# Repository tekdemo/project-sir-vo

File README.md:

SirVo Project
=============

A servo motor replacement board that runs a magnetic encoder for continuous rotation without loss of tracking. Runs the Arduino environment on an embedded Atmega 328, exposing hardware PWM capture, I2C, and UART to a 4 wire input cable.

Additionally, allows for a header on the back of the motor controller, with the intention that you could include "backpacks" that extend the functionality much like you do with an Arduino Shield. 

Uses OpenServo board footprint, which should fit some medium size servo controllers. Tested on Parallax Continuus Rotation Servo, and looks like it should fit TowerPro MG995 servos (which require modifications for continuous rotation).

Currently in the testing phase, with several known flaws in the hardware

Known Bugs
============

- H bridge needs a proper driver for operation with higher input voltages. 

- Voltage regulator isn't performing satisfactorially, and needs to be replaced. Currently requires external 3.3V supply to function.

- Code still very unfinished (and hence, not posted). The exception is the [AS5050 Library](https://github.com/tekdemo/AS5050), which is reasonably functional.

- Motor slot alignments are still not known to function on all brands of servos, but work well for now.

- This uses a very strange passive multiplexing scheme I hacked together for the I2C and UART lines. It's been confirmed to work for UART data transmissions, but I2C is still untested.

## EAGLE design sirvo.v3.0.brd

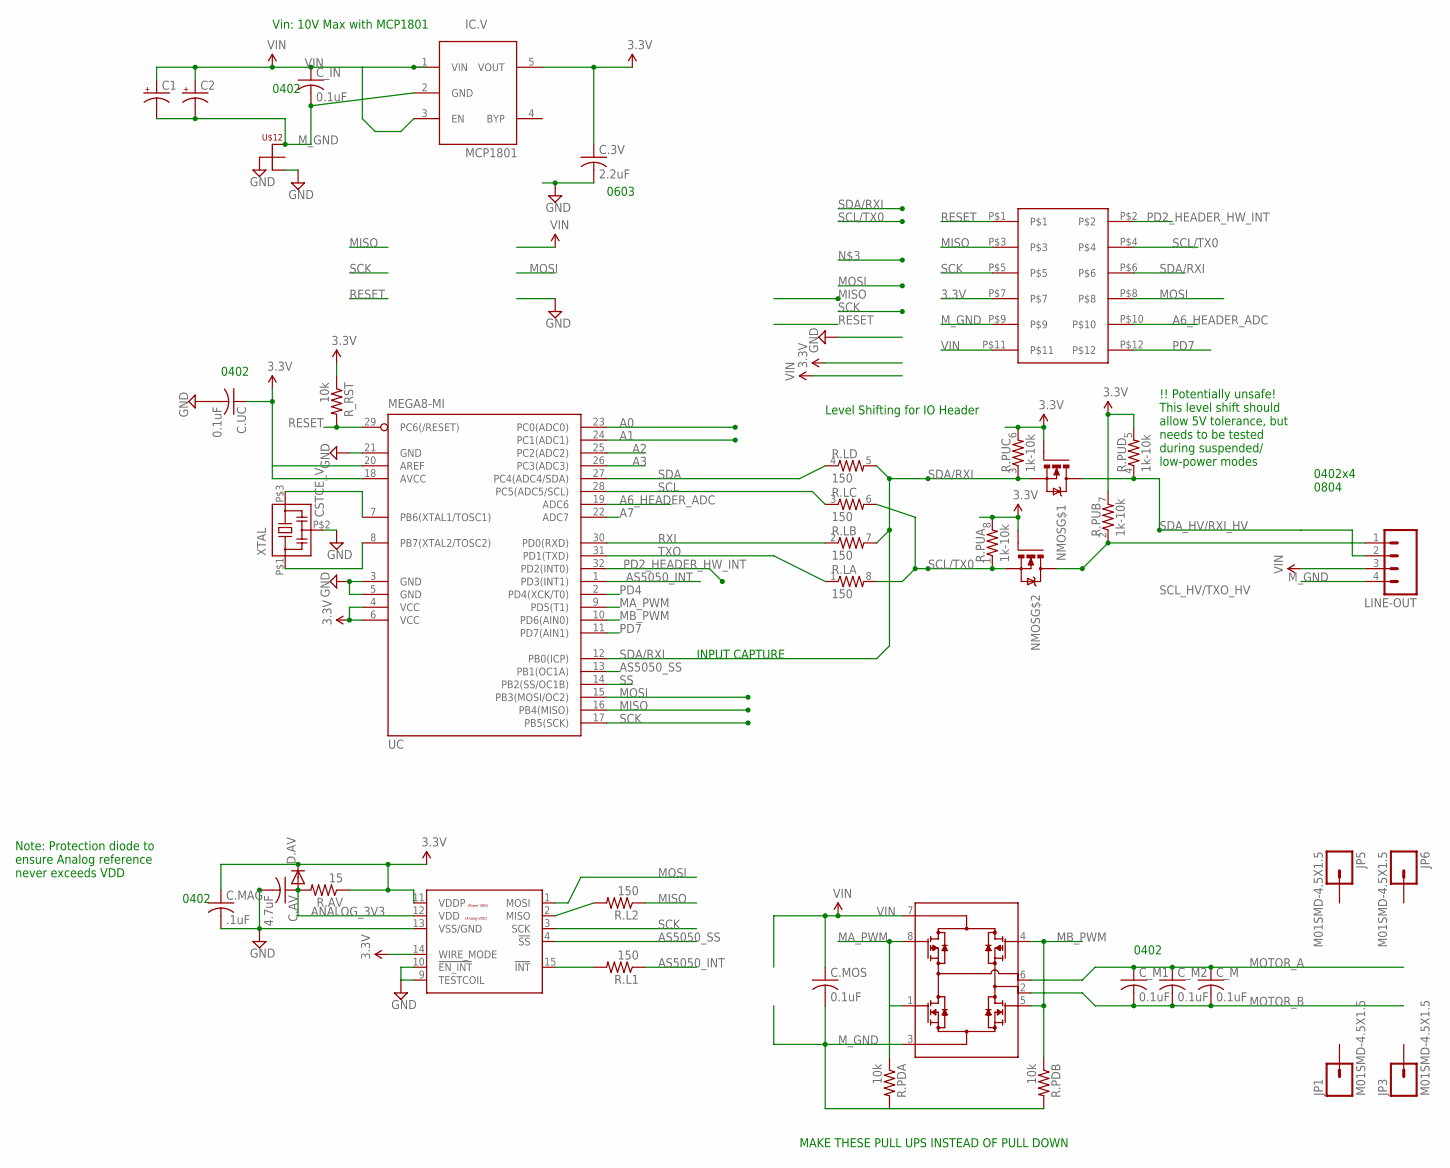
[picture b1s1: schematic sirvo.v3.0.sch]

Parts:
<HEADER>: M06X022MM_SMT; M2X06_SMD
C1: CAP_POLPTH2; CPOL-RADIAL-10UF-25V
C2: CAP_POLC; PANASONIC_C
C.3V: 2.2uF; C0603
C.AV: 4.7uF; C0603
C.MAG: .1uF; C0402
C.MOS, C.UC: 0.1uF; C0402
C_IN: 0.1uF; C0402
C_M, C_M1, C_M2: 0.1uF; C0402
D.AV: DIODESOD; SOD-323
IC.V: MCP1801; SOT23-5L
JP1, JP3, JP5, JP6: M01SMD-4.5X1.5; PAD-1.5X4.5
LINE-OUT: M041X04_NO_SILK; 1X04_NO_SILK
MAG: AS5050; QFN16_4X4
MOS: MOSFET-ARRAYMOSFET-ARRAY-H-BRIDGE; SO08
NMOS: MOSFET-ARRAY-PAIR; SOT-363
R.AV: 15; 0402-RES
R.L: 150; 0603-ARV
R.L1, R.L2: 150; 0402-RES
R.PDA, R.PDB: 10k; 0402-RES
R.PU: 1k-10k; 0603-ARV
R_RST: 10k; 0402-RES
U$12: NET-JUNCTION8-MIL-DIAMETER; NET-JUNCTION
UC: MEGA8-MI; MLF32
XTAL: CSTCE_V

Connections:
3.3V: <HEADER>.P$7, C.3V.1, C.MAG.1, C.UC.1, D.AV.1 (C), IC.V.5 (VOUT), MAG.11 (VDDP), MAG.14 (WIRE_MODE), NMOS.P$2 (G), NMOS.P$5 (G), R.AV.1, R.PU.5 (2), R.PU.6 (2), R.PU.7 (2), R.PU.8 (2), R_RST.1, UC.4 (VCC), UC.6 (VCC), UC.20 (AREF)
A0: UC.23 (PC0(ADC0))
A1: UC.24 (PC1(ADC1))
A2: UC.25 (PC2(ADC2))
A3: UC.26 (PC3(ADC3))
A6_HEADER_ADC: <HEADER>.P$10, UC.19 (ADC6)
A7: UC.22 (ADC7)
ANALOG_3V3: C.AV.1, D.AV.2 (A), MAG.12 (VDD), R.AV.2
AS5050_INT: R.L1.1, UC.1 (PD3(INT1))
AS5050_SS: MAG.4 (!SS), UC.13 (PB1(OC1A))
GND: C.3V.2, C.AV.2, C.MAG.2, C.UC.2, MAG.9 (TESTCOIL), MAG.10 (!EN_INT), MAG.13 (VSS/GND), U$12.P$1 (1), U$12.P$4 (3), UC.3 (GND), UC.5 (GND), UC.21 (GND), XTAL.P$2 (2)
MA_PWM: MOS.1 (N1G), MOS.8 (P1G), R.PDA.1, UC.9 (PD5(T1))
MB_PWM: MOS.4 (N2G), MOS.5 (P2G), R.PDB.1, UC.10 (PD6(AIN0))
MISO: <HEADER>.P$3, R.L2.1, UC.16 (PB4(MISO))
MOSI: <HEADER>.P$8, MAG.1 (MOSI), UC.15 (PB3(MOSI/OC2))
MOTOR_A: C_M.1, C_M1.1, C_M2.1, MOS.6 (N2D/P2D)
MOTOR_B: C_M.2, C_M1.2, C_M2.2, MOS.2 (N1D/P1D)
M_GND: <HEADER>.P$9, C1.2 (-), C2.-, C.MOS.2, C_IN.2, IC.V.2 (GND), LINE-OUT.4, MOS.3 (N1S/N2S), R.PDA.2, R.PDB.2, U$12.P$3 (2)
unnamed: UC.7 (PB6(XTAL1/TOSC1)), XTAL.P$3 (3)
unnamed: UC.8 (PB7(XTAL2/TOSC2)), XTAL.P$1 (1)
unnamed: MAG.15 (!INT), R.L1.2
unnamed: MAG.2 (MISO), R.L2.2
PD2_HEADER_HW_INT: <HEADER>.P$2, UC.32 (PD2(INT0))
PD4: UC.2 (PD4(XCK/T0))
PD7: <HEADER>.P$12, UC.11 (PD7(AIN1))
RESET: <HEADER>.P$1, R_RST.2, UC.29 (PC6(/RESET))
RXI: R.L.2 (1), UC.30 (PD0(RXD))
SCK: <HEADER>.P$5, MAG.3 (SCK), UC.17 (PB5(SCK))
SCL: R.L.3 (1), UC.28 (PC5(ADC5/SCL))
SCL/TX0: <HEADER>.P$4, NMOS.P$1 (S), R.L.6 (2), R.L.8 (2), R.PU.1
SCL_HV/TXO_HV: LINE-OUT.1, NMOS.P$6 (D), R.PU.2 (1)
SDA: R.L.4 (1), UC.27 (PC4(ADC4/SDA))
SDA/RXI: <HEADER>.P$6, NMOS.P$4 (S), R.L.5 (2), R.L.7 (2), R.PU.3 (1), UC.12 (PB0(ICP))
SDA_HV/RXI_HV: LINE-OUT.2, NMOS.P$3 (D), R.PU.4 (1)
SS: UC.14 (PB2(SS/OC1B))
TXO: R.L.1, UC.31 (PD1(TXD))
VIN: <HEADER>.P$11, C1.1 (+), C2.+, C.MOS.1, C_IN.1, IC.V.1 (VIN), IC.V.3 (EN), LINE-OUT.3, MOS.7 (P1S/P2S)

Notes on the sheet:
Level Shifting for IO Header
Vin: 10V Max with MCP1801
0402
0603
0402x4 0804
INPUT CAPTURE
Note: Protection diode to ensure Analog reference never exceeds VDD
!! Potentially unsafe! This level shift should allow 5V tolerance, but needs to be tested during suspended/ low-power modes
MAKE THESE PULL UPS INSTEAD OF PULL DOWN

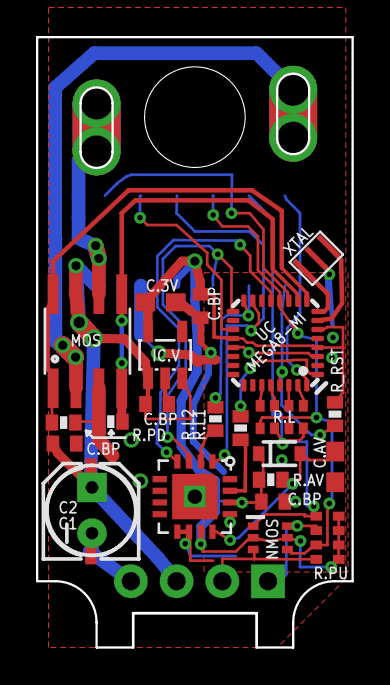
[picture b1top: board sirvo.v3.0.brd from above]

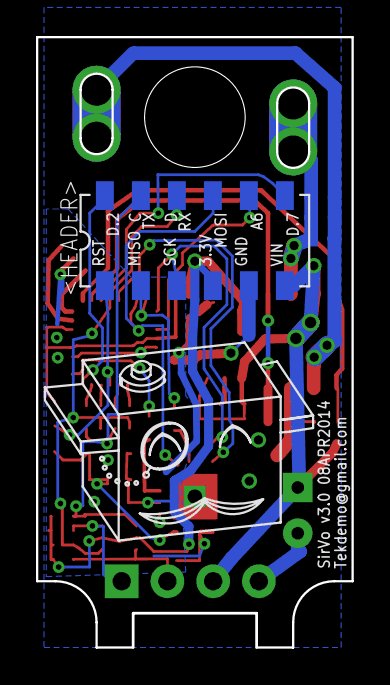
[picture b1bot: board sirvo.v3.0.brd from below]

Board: 2 copper layers, 17.5 x 33.9 mm, 35 parts (7 on the bottom side), 30 nets.

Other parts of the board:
U$1: LOGO-SIRVO-GOLD
U$3: SERVO-OUTLINE

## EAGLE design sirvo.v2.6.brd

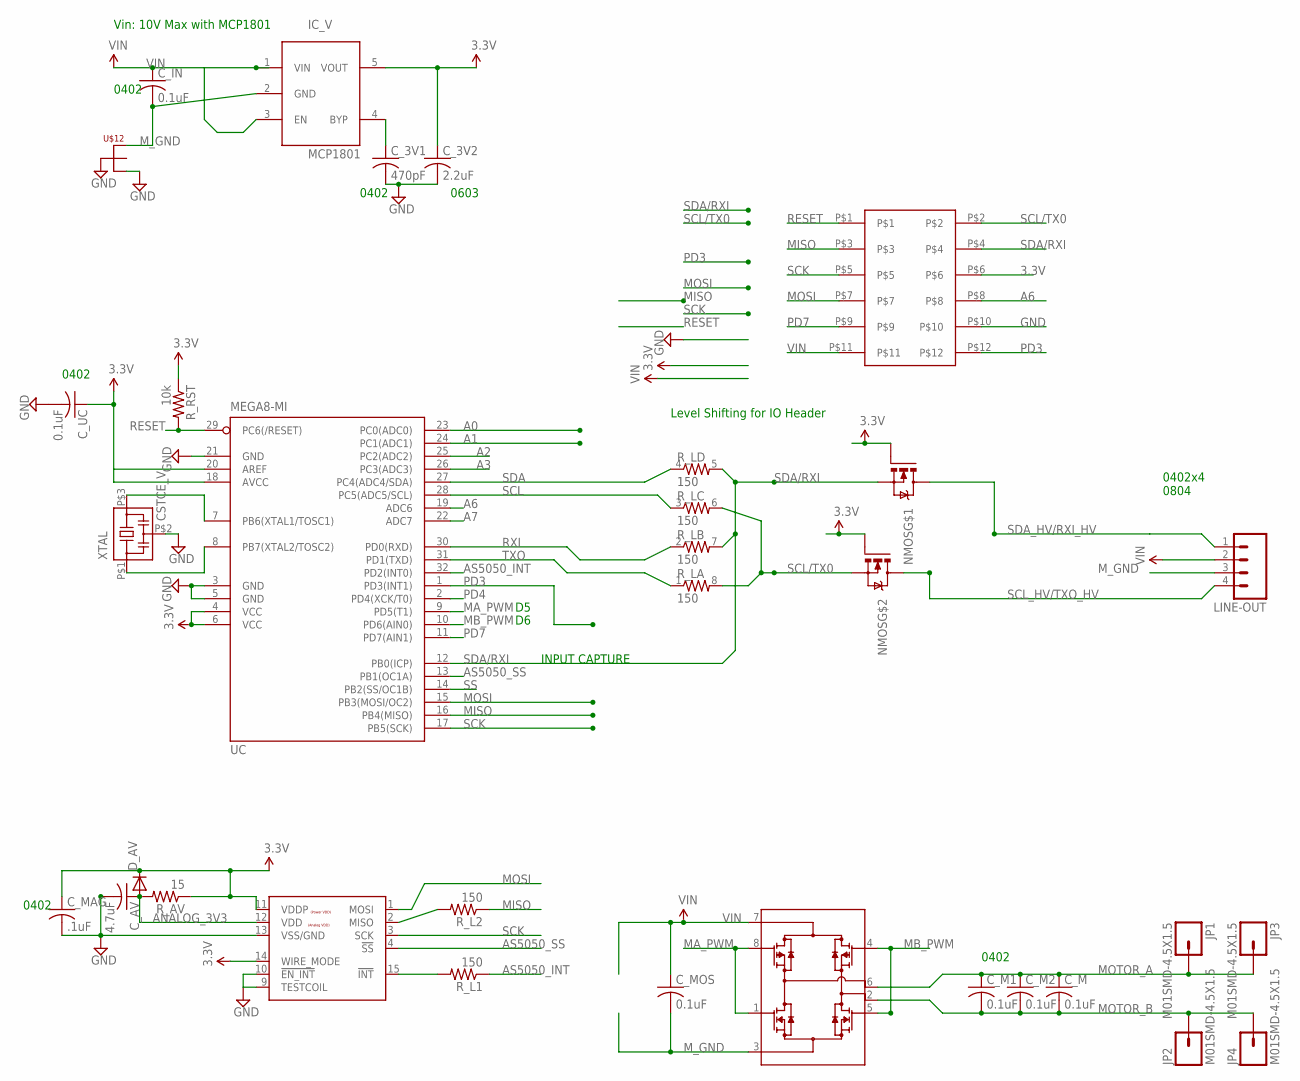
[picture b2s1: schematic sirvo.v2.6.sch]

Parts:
<HEADER>: M06X022MM_SMT; M2X06_SMD
C_3V1: 470pF; C0402
C_3V2: 2.2uF; C0603
C_AV: 4.7uF; C0603
C_IN: 0.1uF; C0402
C_M, C_M1, C_M2: 0.1uF; C0402
C_MAG: .1uF; C0402
C_MOS: 0.1uF; C0402
C_UC: 0.1uF; C0402
D_AV: DIODESOD; SOD-323
IC_V: MCP1801; SOT23-5L
JP1, JP2, JP3, JP4: M01SMD-4.5X1.5; PAD-1.5X4.5
LINE-OUT: M041X04_NO_SILK; 1X04_NO_SILK
MAG: AS5050; QFN16_4X4
MOS: MOSFET-ARRAYMOSFET-ARRAY-H-BRIDGE; SO08
NMOS: MOSFET-ARRAY-PAIR; SOT-363
R_AV: 15; 0603-RES
R_L: 150; 0603-ARV
R_L1, R_L2: 150; 0402-RES
R_RST: 10k; 0603-RES
U$12: NET-JUNCTION8-MIL-DIAMETER; NET-JUNCTION
UC: MEGA8-MI; MLF32
XTAL: CSTCE_V

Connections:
3.3V: <HEADER>.P$6, C_3V2.1, C_MAG.1, C_UC.1, D_AV.1 (C), IC_V.5 (VOUT), MAG.11 (VDDP), MAG.14 (WIRE_MODE), NMOS.P$2 (G), NMOS.P$5 (G), R_AV.1, R_RST.1, UC.4 (VCC), UC.6 (VCC), UC.20 (AREF)
A0: UC.23 (PC0(ADC0))
A1: UC.24 (PC1(ADC1))
A2: UC.25 (PC2(ADC2))
A3: UC.26 (PC3(ADC3))
A6: <HEADER>.P$8, UC.19 (ADC6)
A7: UC.22 (ADC7)
ANALOG_3V3: C_AV.1, D_AV.2 (A), MAG.12 (VDD), R_AV.2
AS5050_INT: R_L1.1, UC.32 (PD2(INT0))
AS5050_SS: MAG.4 (!SS), UC.13 (PB1(OC1A))
GND: <HEADER>.P$10, C_3V1.2, C_3V2.2, C_AV.2, C_MAG.2, C_UC.2, MAG.9 (TESTCOIL), MAG.10 (!EN_INT), MAG.13 (VSS/GND), U$12.P$1 (1), U$12.P$4 (3), UC.3 (GND), UC.5 (GND), UC.21 (GND), XTAL.P$2 (2)
MA_PWM: MOS.1 (N1G), MOS.8 (P1G), UC.9 (PD5(T1))
MB_PWM: MOS.4 (N2G), MOS.5 (P2G), UC.10 (PD6(AIN0))
MISO: <HEADER>.P$3, R_L2.1, UC.16 (PB4(MISO))
MOSI: <HEADER>.P$7, MAG.1 (MOSI), UC.15 (PB3(MOSI/OC2))
MOTOR_A: C_M.1, C_M1.1, C_M2.1, JP1.P$1, JP3.P$1, MOS.6 (N2D/P2D)
MOTOR_B: C_M.2, C_M1.2, C_M2.2, JP2.P$1, JP4.P$1, MOS.2 (N1D/P1D)
M_GND: C_IN.2, C_MOS.2, IC_V.2 (GND), LINE-OUT.3, MOS.3 (N1S/N2S), U$12.P$3 (2)
unnamed: UC.7 (PB6(XTAL1/TOSC1)), XTAL.P$3 (3)
unnamed: UC.8 (PB7(XTAL2/TOSC2)), XTAL.P$1 (1)
unnamed: C_3V1.1, IC_V.4 (BYP)
unnamed: MAG.15 (!INT), R_L1.2
unnamed: MAG.2 (MISO), R_L2.2
PD3: <HEADER>.P$12, UC.1 (PD3(INT1))
PD4: UC.2 (PD4(XCK/T0))
PD7: <HEADER>.P$9, UC.11 (PD7(AIN1))
RESET: <HEADER>.P$1, R_RST.2, UC.29 (PC6(/RESET))
RXI: R_L.2 (1), UC.30 (PD0(RXD))
SCK: <HEADER>.P$5, MAG.3 (SCK), UC.17 (PB5(SCK))
SCL: R_L.3 (1), UC.28 (PC5(ADC5/SCL))
SCL/TX0: <HEADER>.P$2, NMOS.P$1 (S), R_L.6 (2), R_L.8 (2)
SCL_HV/TXO_HV: LINE-OUT.4, NMOS.P$6 (D)
SDA: R_L.4 (1), UC.27 (PC4(ADC4/SDA))
SDA/RXI: <HEADER>.P$4, NMOS.P$4 (S), R_L.5 (2), R_L.7 (2), UC.12 (PB0(ICP))
SDA_HV/RXI_HV: LINE-OUT.1, NMOS.P$3 (D)
SS: UC.14 (PB2(SS/OC1B))
TXO: R_L.1, UC.31 (PD1(TXD))
VIN: <HEADER>.P$11, C_IN.1, C_MOS.1, IC_V.1 (VIN), IC_V.3 (EN), LINE-OUT.2, MOS.7 (P1S/P2S)

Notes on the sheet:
Level Shifting for IO Header
Vin: 10V Max with MCP1801
0402
0603
0402x4 0804
INPUT CAPTURE

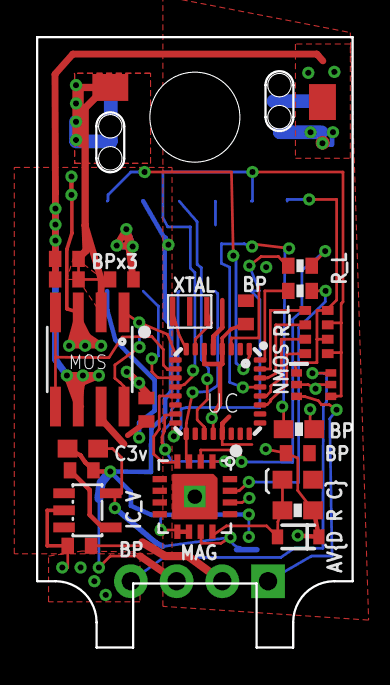
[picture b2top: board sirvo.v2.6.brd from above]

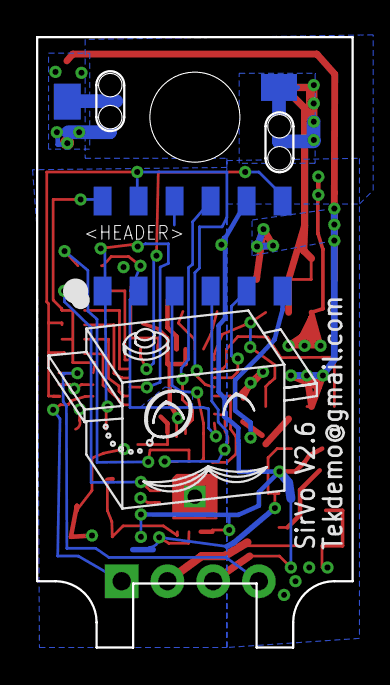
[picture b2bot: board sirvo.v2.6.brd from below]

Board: 2 copper layers, 17.5 x 33.9 mm, 31 parts (5 on the bottom side), 31 nets.

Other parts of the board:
U$1: LOGO-SIRVO-GOLD
U$3: SERVO-OUTLINE

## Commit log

2014-03-05 Fixed Readme
2014-04-08 Initial rerouting, everything but header
2014-04-08 Finished routing of all on-board signals
    Header routing not yet completed
2014-04-08 Remove the v2.6 board file, switch to v3.0
    I know this isn't how you git, but it was an old naming scheme DON'T JUDGE ME.
2014-04-09 Added header routing and silkscreen
2014-04-09 Routed Headers, added header pinout in silk
2014-04-09 Board as-ordered for revision 3.0
2014-05-27 verified functionality of board, added notes
2014-05-27 Updated readme file

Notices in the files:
parts and their libraries:
SparkFun-Passives: Licensing: CC v3.0 Share-Alike You are welcome to use this library for commercial purposes.
